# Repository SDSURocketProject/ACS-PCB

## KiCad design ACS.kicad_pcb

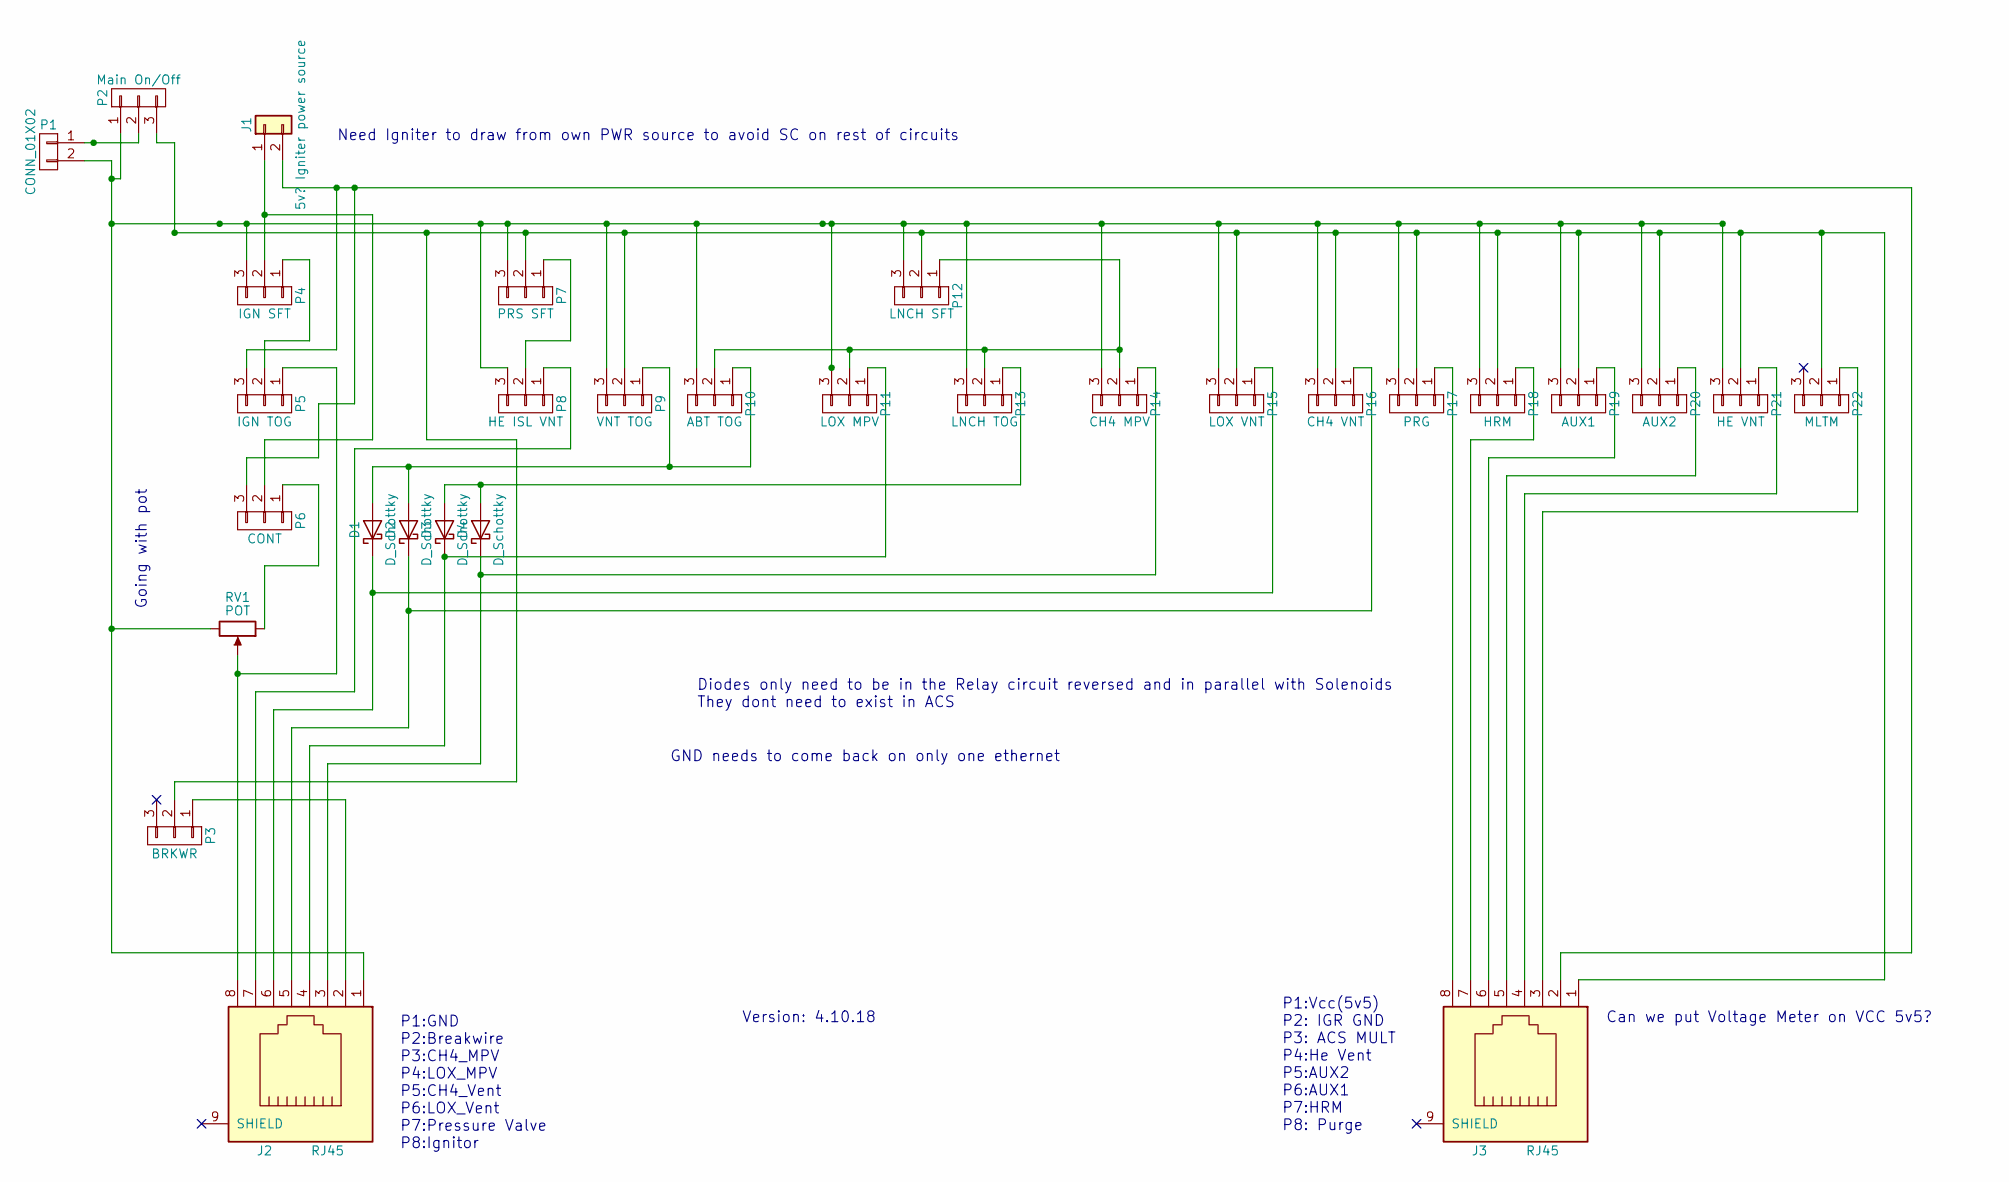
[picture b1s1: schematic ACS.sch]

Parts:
D1, D2, D3, D4: D_Schottky; D_0603
J1: 5v? Igniter power source; MolexFemale
J2, J3: RJ45; rj45 ethernet
P1: CONN_01X02; MolexFemale
P2: Main On/Off; JST_XH_B03B-XH-A_03x2.50mm_Straight
P3: BRKWR; JST_XH_B03B-XH-A_03x2.50mm_Straight
P4: IGN SFT; JST_XH_B03B-XH-A_03x2.50mm_Straight
P5: IGN TOG; JST_XH_B03B-XH-A_03x2.50mm_Straight
P6: CONT; JST_XH_B03B-XH-A_03x2.50mm_Straight
P7: PRS SFT; JST_XH_B03B-XH-A_03x2.50mm_Straight
P8: HE ISL VNT; JST_XH_B03B-XH-A_03x2.50mm_Straight
P9: VNT TOG; JST_XH_B03B-XH-A_03x2.50mm_Straight
P10: ABT TOG; JST_XH_B03B-XH-A_03x2.50mm_Straight
P11: LOX MPV; JST_XH_B03B-XH-A_03x2.50mm_Straight
P12: LNCH SFT; JST_XH_B03B-XH-A_03x2.50mm_Straight
P13: LNCH TOG; JST_XH_B03B-XH-A_03x2.50mm_Straight
P14: CH4 MPV; JST_XH_B03B-XH-A_03x2.50mm_Straight
P15: LOX VNT; JST_XH_B03B-XH-A_03x2.50mm_Straight
P16: CH4 VNT; JST_XH_B03B-XH-A_03x2.50mm_Straight
P17: PRG; JST_XH_B03B-XH-A_03x2.50mm_Straight
P18: HRM; JST_XH_B03B-XH-A_03x2.50mm_Straight
P19: AUX1; JST_XH_B03B-XH-A_03x2.50mm_Straight
P20: AUX2; JST_XH_B03B-XH-A_03x2.50mm_Straight
P21: HE VNT; JST_XH_B03B-XH-A_03x2.50mm_Straight
P22: MLTM; JST_XH_B03B-XH-A_03x2.50mm_Straight
RV1: POT; Potentiometer_Trimmer_Vishay_T73XW_Vertical

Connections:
unnamed: D1.1 (K), J2.6, P15.1
unnamed: D1.2 (A), D2.2 (A), P9.1, P10.1
unnamed: D2.1 (K), J2.5, P16.1
unnamed: D3.1 (K), J2.4, P11.1
unnamed: D3.2 (A), D4.2 (A), P13.1
unnamed: D4.1 (K), J2.3, P14.1
unnamed: J1.1, P4.2, P6.2
unnamed: J1.2, J3.2, P5.3, P6.3
unnamed: J2.1, P1.2, P2.1, P4.3, P7.3, P8.3, P9.3, P10.3, P11.3, P12.3, P13.3, P14.3, P15.3, P16.3, P17.3, P18.3, P19.3, P20.3, P21.3, RV1.3
unnamed: J2.2, P3.1
unnamed: J2.7, P8.1
unnamed: J2.8, P5.1, RV1.2
unnamed: J3.1, P2.3, P3.2, P7.2, P9.2, P12.2, P15.2, P16.2, P17.2, P18.2, P19.2, P20.2, P21.2, P22.2
unnamed: J3.3, P22.1
unnamed: J3.4, P21.1
unnamed: J3.5, P20.1
unnamed: J3.6, P19.1
unnamed: J3.7, P18.1
unnamed: J3.8, P17.1
unnamed: P1.1, P2.2
unnamed: P4.1, P5.2
unnamed: P6.1, RV1.1
unnamed: P7.1, P8.2
unnamed: P10.2, P11.2, P12.1, P13.2, P14.2

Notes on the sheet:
P1:GND P2:Breakwire P3:CH4_MPV P4:LOX_MPV P5:CH4_Vent P6:LOX_Vent P7:Pressure Valve P8:Ignitor
Can we put Voltage Meter on VCC 5v5?
Need Igniter to draw from own PWR source to avoid SC on rest of circuits
Diodes only need to be in the Relay circuit reversed and in parallel with Solenoids They dont need to exist in ACS
P1:Vcc(5v5) P2: IGR GND P3: ACS MULT P4:He Vent P5:AUX2 P6:AUX1 P7:HRM P8: Purge
GND needs to come back on only one ethernet
Going with pot
Version: 4.10.18

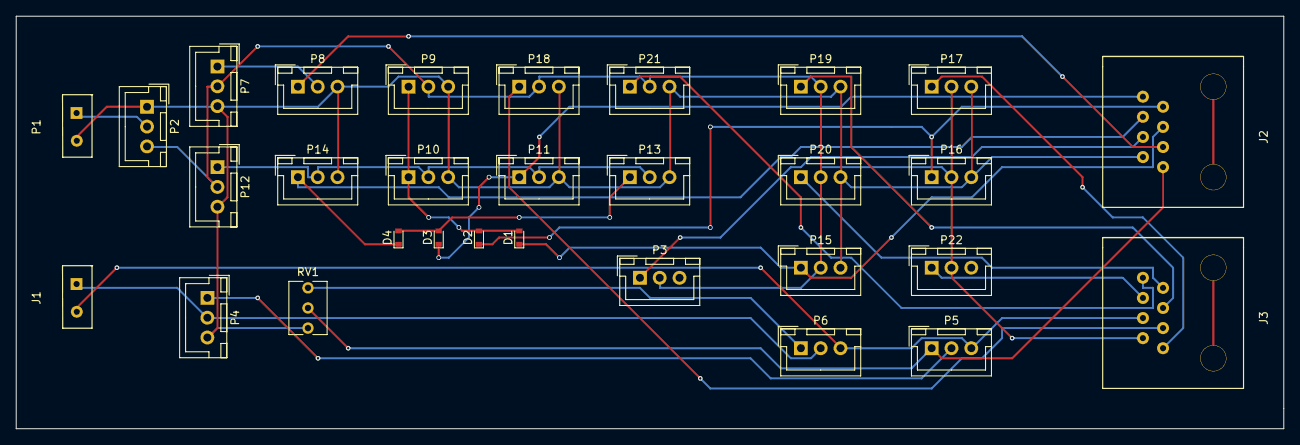
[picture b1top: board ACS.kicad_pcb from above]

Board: 2 copper layers, 160.0 x 52.1 mm, 30 parts (0 on the bottom side), 24 nets.

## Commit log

2018-04-10 add the things
2018-04-10 Added version number
2018-04-10 Trimmer Resistor, finished circuit
2018-04-11 Footprint and Schematic finished, traces started
2018-04-12 Finished traces, and edge border
2018-04-13 add altium stuff
2018-04-14 Added relay station
2018-04-14 Added Relay Station x2
2019-02-27 Update to rev 4.0.0 - Back plane is now SGND rather than GND - Increased VCC trace width to 20mil - Remove GND routes to make space for other traces, and decrease via usage
2019-04-14 final review from cade
2019-04-15 add new gerber files
2019-04-15 Add zip of gerber files
